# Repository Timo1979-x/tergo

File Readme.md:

### Preparation
- TBD...
- After cloning git repository, go to Kicad path variables and define variable `TERGO_LIBS` to point to <repo>/pcb/common/libs, i.e.: `TERGO_LIBS => /home/tim/work/qmk_firmware/keyboards/tergo/pcb/common/libs`

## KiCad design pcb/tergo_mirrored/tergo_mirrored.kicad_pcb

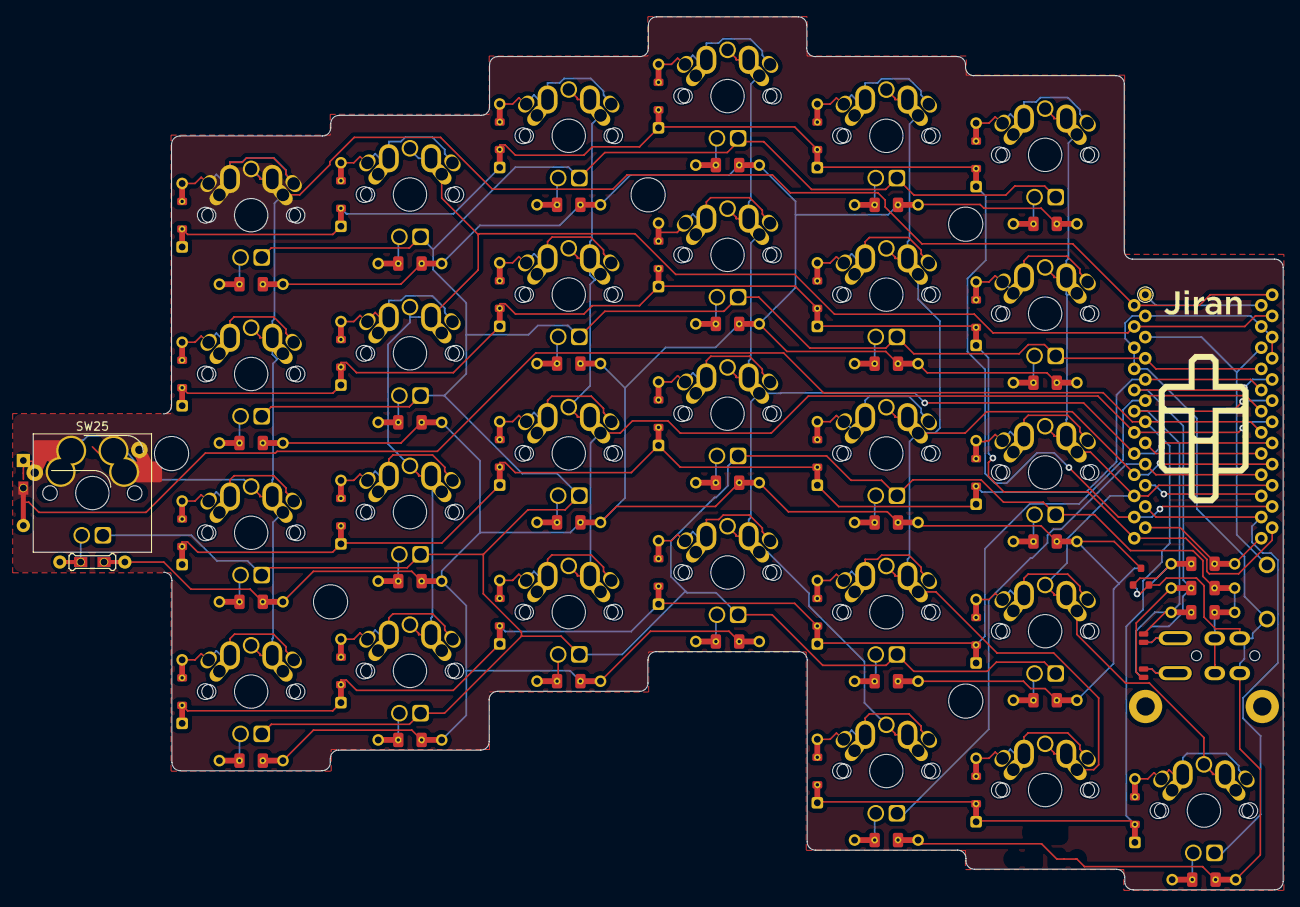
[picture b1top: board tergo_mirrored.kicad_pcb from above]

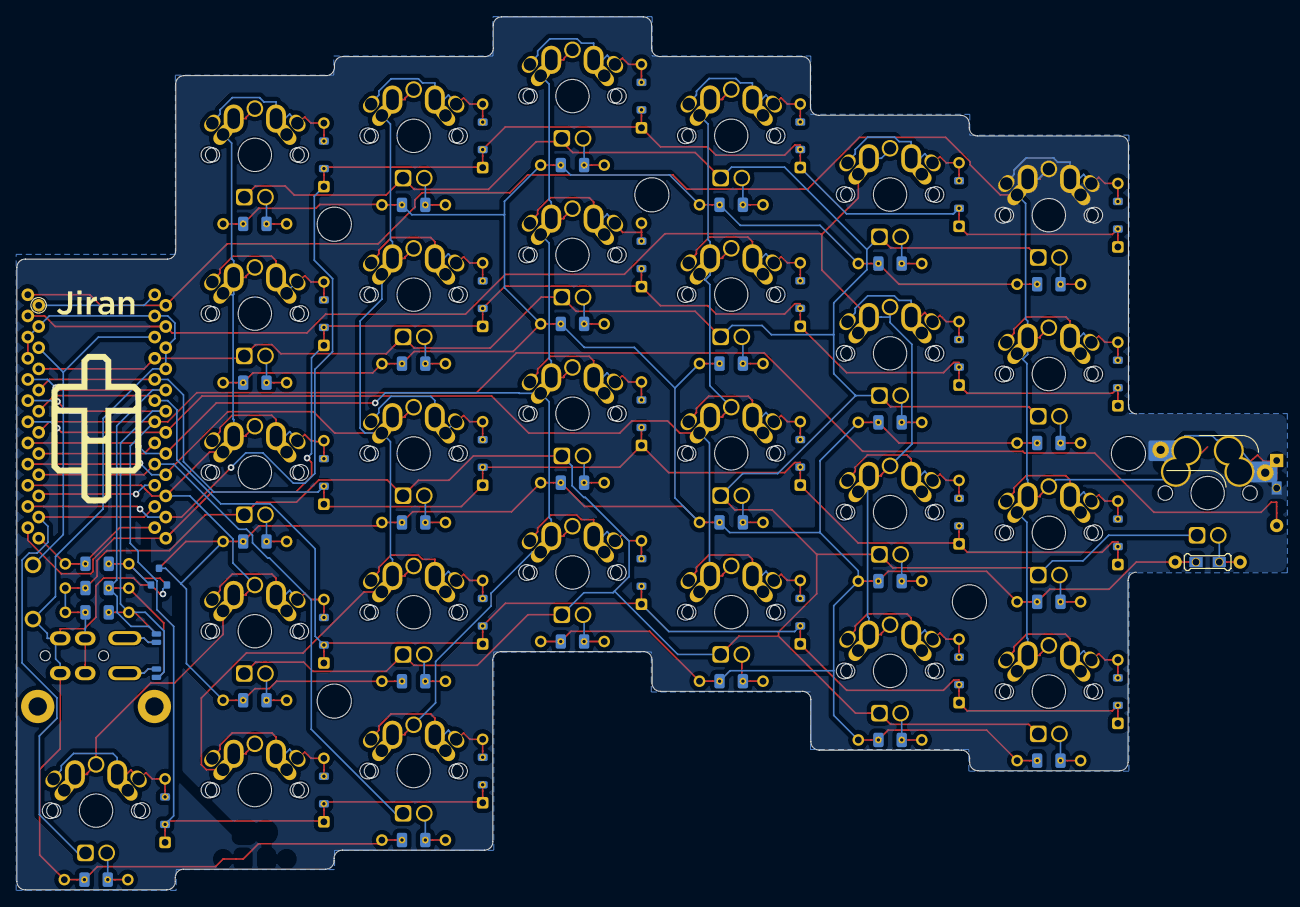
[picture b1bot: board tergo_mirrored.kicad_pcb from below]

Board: 2 copper layers, 134.3 x 104.7 mm, 130 parts (3 on the bottom side), 77 nets.

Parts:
D1, D2, D3, D4, D5, D6, D7, D8, D9, D10, D11, D12, D13, D14, D15, D16, D17, D18, D19, D20, D21, D22, D23, D24, D26, D27, D28: 1N4148; Diode_Hybrid_SOD-123
D25: 1N4148; Diode-Hybrid-2sided
D29, D30, D31, D32, D33, D34, D35, D36, D37, D38, D39, D40, D41, D42, D43, D44, D45, D46, D47, D48, D49, D50, D51, D52, D53, D54, D56: LED_Small; LED
G1, G2: LOGO; Silk_Logo_Old
H1, H2, H3, H6, H7: CaseHole; MountHole
H8, H9: CoverHole
J1: TRRS; TRSS_DUAL_THT
JP2, JP3, JP4, JP5: Jumper; jumper
Q1: 2N7002; SOT-23
R1, R2, R3, R4, R5, R6, R7, R8, R9, R10, R11, R12, R13, R14, R15, R16, R17, R18, R19, R20, R21, R22, R23, R24, R26, R28: 330R; Resistor_Hybrid_1205
R25: 330R; Resistor-Hybrid-2sided
R29, R30: 4.7k; Resistor_Hybrid_1205
R31: 10k; Resistor_Hybrid_1205
SW1, SW2: SW2; Switch_MxAlpsChoc_MillMax_1u
SW3, SW4, SW5, SW6, SW7, SW8, SW9, SW10, SW11, SW12, SW13, SW14, SW15, SW16, SW17, SW18, SW19, SW20, SW21, SW22, SW23, SW24, SW26, SW27, SW28: SW_Push; Switch_MxAlpsChoc_MillMax_1u
SW25: SW_Push; SW_Hotswap_Kailh_MX_Plated_mirrored2_1.00u
SW29: SW_Push; Reset_Switch
U1: ProMicro; ProMicro_TwoSide

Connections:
/CAPS: D54.2, U1.16
/LED: R31.2, U1.13
/LEDOut: Q1.3, R1.2, R2.2, R3.2, R4.2, R5.2, R6.2, R7.2, R8.2, R9.2, R10.2, R11.2, R12.2, R13.2, R14.2, R15.2, R16.2, R17.2, R18.2, R19.2, R20.2, R21.2, R22.2, R23.2, R24.2, R25.2
/NUM: D56.2, U1.14
/col0: SW7.2, SW13.2, SW19.2, SW25.2, U1.1
/col1: SW1.2, SW2.2, SW8.2, SW14.2, SW20.2, U1.2
/col2: SW3.2, SW9.2, SW15.2, SW21.2, U1.7
/col3: SW4.2, SW10.2, SW16.2, SW22.2, SW26.2, U1.8
/col4: SW5.2, SW11.2, SW17.2, SW23.2, SW27.2, U1.9
/col5: SW6.2, SW12.2, SW18.2, SW24.2, SW28.2, U1.10
/rowA: D1.1, D2.1, D3.1, D4.1, D5.1, D6.1, U1.11
/rowB: D7.1, D8.1, D9.1, D10.1, D11.1, D12.1, U1.12
/rowC: D13.1, D14.1, D15.1, D16.1, D17.1, D18.1, U1.20
/rowD: D19.1, D20.1, D21.1, D22.1, D23.1, D24.1, U1.19
/rowE: D25.1, D26.1, D27.1, D28.1, U1.18
GND: J1.B, Q1.2, R26.2, R28.2, SW29.2, U1.3, U1.4, U1.23
unnamed: D2.2, SW1.1, SW2.1
unnamed: D3.2, SW3.1
unnamed: D4.2, SW4.1
unnamed: D5.2, SW5.1
unnamed: D6.2, SW6.1
unnamed: D7.2, SW7.1
unnamed: D8.2, SW8.1
unnamed: D9.2, SW9.1
unnamed: D10.2, SW10.1
unnamed: D11.2, SW11.1
unnamed: D12.2, SW12.1
unnamed: D13.2, SW13.1
unnamed: D14.2, SW14.1
unnamed: D15.2, SW15.1
unnamed: D16.2, SW16.1
unnamed: D17.2, SW17.1
unnamed: D18.2, SW18.1
unnamed: D19.2, SW19.1
unnamed: D20.2, SW20.1
unnamed: D21.2, SW21.1
unnamed: D22.2, SW22.1
unnamed: D23.2, SW23.1
unnamed: D24.2, SW24.1
unnamed: D25.2, SW25.1
unnamed: D26.2, SW26.1
unnamed: D27.2, SW27.1
unnamed: D28.2, SW28.1
unnamed: D29.1, R1.1
unnamed: D30.1, R2.1
unnamed: D31.1, R3.1
unnamed: D32.1, R4.1
unnamed: D33.1, R5.1
unnamed: D34.1, R6.1
unnamed: D35.1, R7.1
unnamed: D36.1, R8.1
unnamed: D37.1, R9.1
unnamed: D38.1, R10.1
unnamed: D39.1, R11.1
unnamed: D40.1, R12.1
unnamed: D41.1, R13.1
unnamed: D42.1, R14.1
unnamed: D43.1, R15.1
unnamed: D44.1, R16.1
unnamed: D45.1, R17.1
unnamed: D46.1, R18.1
unnamed: D47.1, R19.1
unnamed: D48.1, R20.1
unnamed: D49.1, R21.1
unnamed: D50.1, R22.1
unnamed: D51.1, R23.1
unnamed: D52.1, R24.1
unnamed: D53.1, R25.1
unnamed: D54.1, R26.1
unnamed: D56.1, R28.1
unnamed: J1.A, JP2.1, JP3.1
unnamed: J1.D, JP4.1, JP5.1
unnamed: Q1.1, R31.1
RST: SW29.1, U1.22
SCL: JP3.2, JP5.2, R30.2, U1.6
SDA: JP2.2, JP4.2, R29.1, U1.5
VCC: D29.2, D30.2, D31.2, D32.2, D33.2, D34.2, D35.2, D36.2, D37.2, D38.2, D39.2, D40.2, D41.2, D42.2, D43.2, D44.2, D45.2, D46.2, D47.2, D48.2, D49.2, D50.2, D51.2, D52.2, D53.2, J1.C, R29.2, R30.1, U1.21

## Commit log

2025-12-22 добавил дополнительный ряд клавиш в раскладку (в схему и в исходник)
2025-12-25 [+] .editorconfig [+] Макросы для печати значения других макросов на этапе компиляции [+] скрипты для преобразования монохромных BMP файлов в байтовые массивы для контроллера ssd1306 [+] в клаву доба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
2026-01-03 Эксперименты...
2026-01-03 fixed schematic ERC errors and warnings refactored some symbols to project-level libraries
2026-01-04 splitted PCB projects into mirror version and full (left+right) version
2026-01-07 wip on PCB
2026-01-08 modified two mirrored MX switches
